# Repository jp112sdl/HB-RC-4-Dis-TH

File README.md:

# HB-RC-4-Dis-TH
## 4fach Wandtaster mit Display und Temperatursensor

Als Vorlage/Idee diente das [AVM FRITZ!DECT 440](https://avm.de/produkte/fritzdect/fritzdect-440/).

### Aufbau:

An den 4 Ecken befinden sich Taster, um über 4 verschiedenen Tasterkanäle Geräte zu steuern.<br/>
Unten mittig ist der Mode-Taster:
- langes Drücken = Anlernen oder (ganz lange) RESET
- kurzes Drücken = Anzeige der Tasterbeschriftung

In Ruhe werden auf dem Display die Temperatur (und wahlweise Luftfeuchtigkeit) sowie der Batteriezustand angezeigt.
Wird der Mode-Taster kurz gedrückt, erscheint für die in den Geräteeinstellungen festgelegte "Display Timeout" Zeit die Taster-Beschriftung.

Als Beschriftung lassen sich
- eine Überschrift (optional)
- 1 bis 2 Zeilen Beschriftungstext

hinterlegen

<br><br>

### Prototyp

Nur Temperaturanzeige:<br>
<br><br>
Temperatur- und Luftfeuchtigkeit:<br>
<br><br>
Tasterbeschriftungen:<br>

### PCB Version 2.1

<br>
**[Abstandhalter](https://github.com/jp112sdl/HB-RC-4-Dis-TH/blob/master/PCB/HB-RC-4-Dis-TH%20ePaper%20Spacer.stl) zwischen Platine und ePaper:**<br/>
<br/>

**erste Version von JLCPCB**

<br/>
<br/>

### CCU:

**Status und Bedienung -> Geräte**<br/>

<br/>
**Einstellungen -> Geräte**<br/>

### Zutaten
| Anzahl LiPo | Anzahl Batt | Bezeichnung | Bauform | Artikelnummer (Reichelt)|
|--------|--------|-------------|----------|---------------|
|6  |6  | 100nF	| 0805	| X7R-G0805 100N
|11	|11	| 1µF/25V	| 0805	| KEM X5R0805 1,0U
|1	|1	| 100µ/10V	| 3528	| TAJ 3528 100/10
|2	|0	| 10µ/10V	| 0805	|KEM X5R0805 10U
|1	|1 | LED rot	| 0805	| OSO LHR974
|1	|1	| LED grün	| 0805	| OSO LGR971
|1	|0	| LED weiß	| 0805	| SLO SMD-W0805-0
|3	|3	| MBR0530	| SOD-123	| MBR0530T1G ONS 
|1	|1	| 68µH	| 3012	| L-1616FPS 68µ
|1	|1	| IRLML 6346 | SOT-23	| IRLML 6346
|1	|1	| ATMEGA 1284P-AU	| TQFP-44	| ATMEGA 1284P-AU
|1  |0  | MCP 1700T-3002E | SOT-23 | MCP 1700T-3002E
|1  |0  | MCP 73831T-2ACI | SOT-23-5 | MCP 73831T-2ACI
|1  |0	| PC357 | SO-4 | PC 357NJ0000F |
|2	|2	| 240	| 0805	| RND 0805 1 240
|1	|0	| 680	| 0805	| RND 0805 1 680
|1	|0	| 1k 	| 0805	| RND 0805 1 1,0K
|1	|0	| 2k2	| 0805	| RND 0805 1 2,2K
|1	|0	| 4k7	| 0805	| RND 0805 1 4,7k
|3	|3	| 10k	| 0805	| RND 0805 1 10K
|3	|1	| 100k	| 0805	| RND 0805 1 100K
|1	|0	| 470k	| 0805	| RND 0805 1 470K
|2	|2	| 1,0	| 0805	| SMD-0805 1,00
|5	|5	| Taster	| THT	| RND 210-00193
|1	|1	| Taster	| SMD	| https://de.aliexpress.com/item/1005001298009129.html
|1	|1	| ZIF-Sockel 24pol.	| ZIF SMD	| EA WF050-24S
|1 |1	| GoodDisplay ePaper 1,54" GDEW0154M09 ||https://de.aliexpress.com/item/4000993819257.html|
|1 |1 | SHT31 Sensor ||https://de.aliexpress.com/item/32850554676.html|
|1	|0	| 600mAh LiPo	| 	| https://www.ebay.de/itm/LiPo-Lithium-Polymer-3-7V-Akku-mit-BMS-PCB-Batterie-Handy-MP3-Tablet-Navi-LiIon/372814314688?ssPageName=STRK%3AMEBIDX%3AIT&var=641708800610 
|1	|0	| Induktionsladeempfänger	1x1,5cm | 	| https://de.aliexpress.com/item/4000086798457.html
|1	|0	| Induktionsladegerät	| 	| https://de.aliexpress.com/item/4000969719130.html

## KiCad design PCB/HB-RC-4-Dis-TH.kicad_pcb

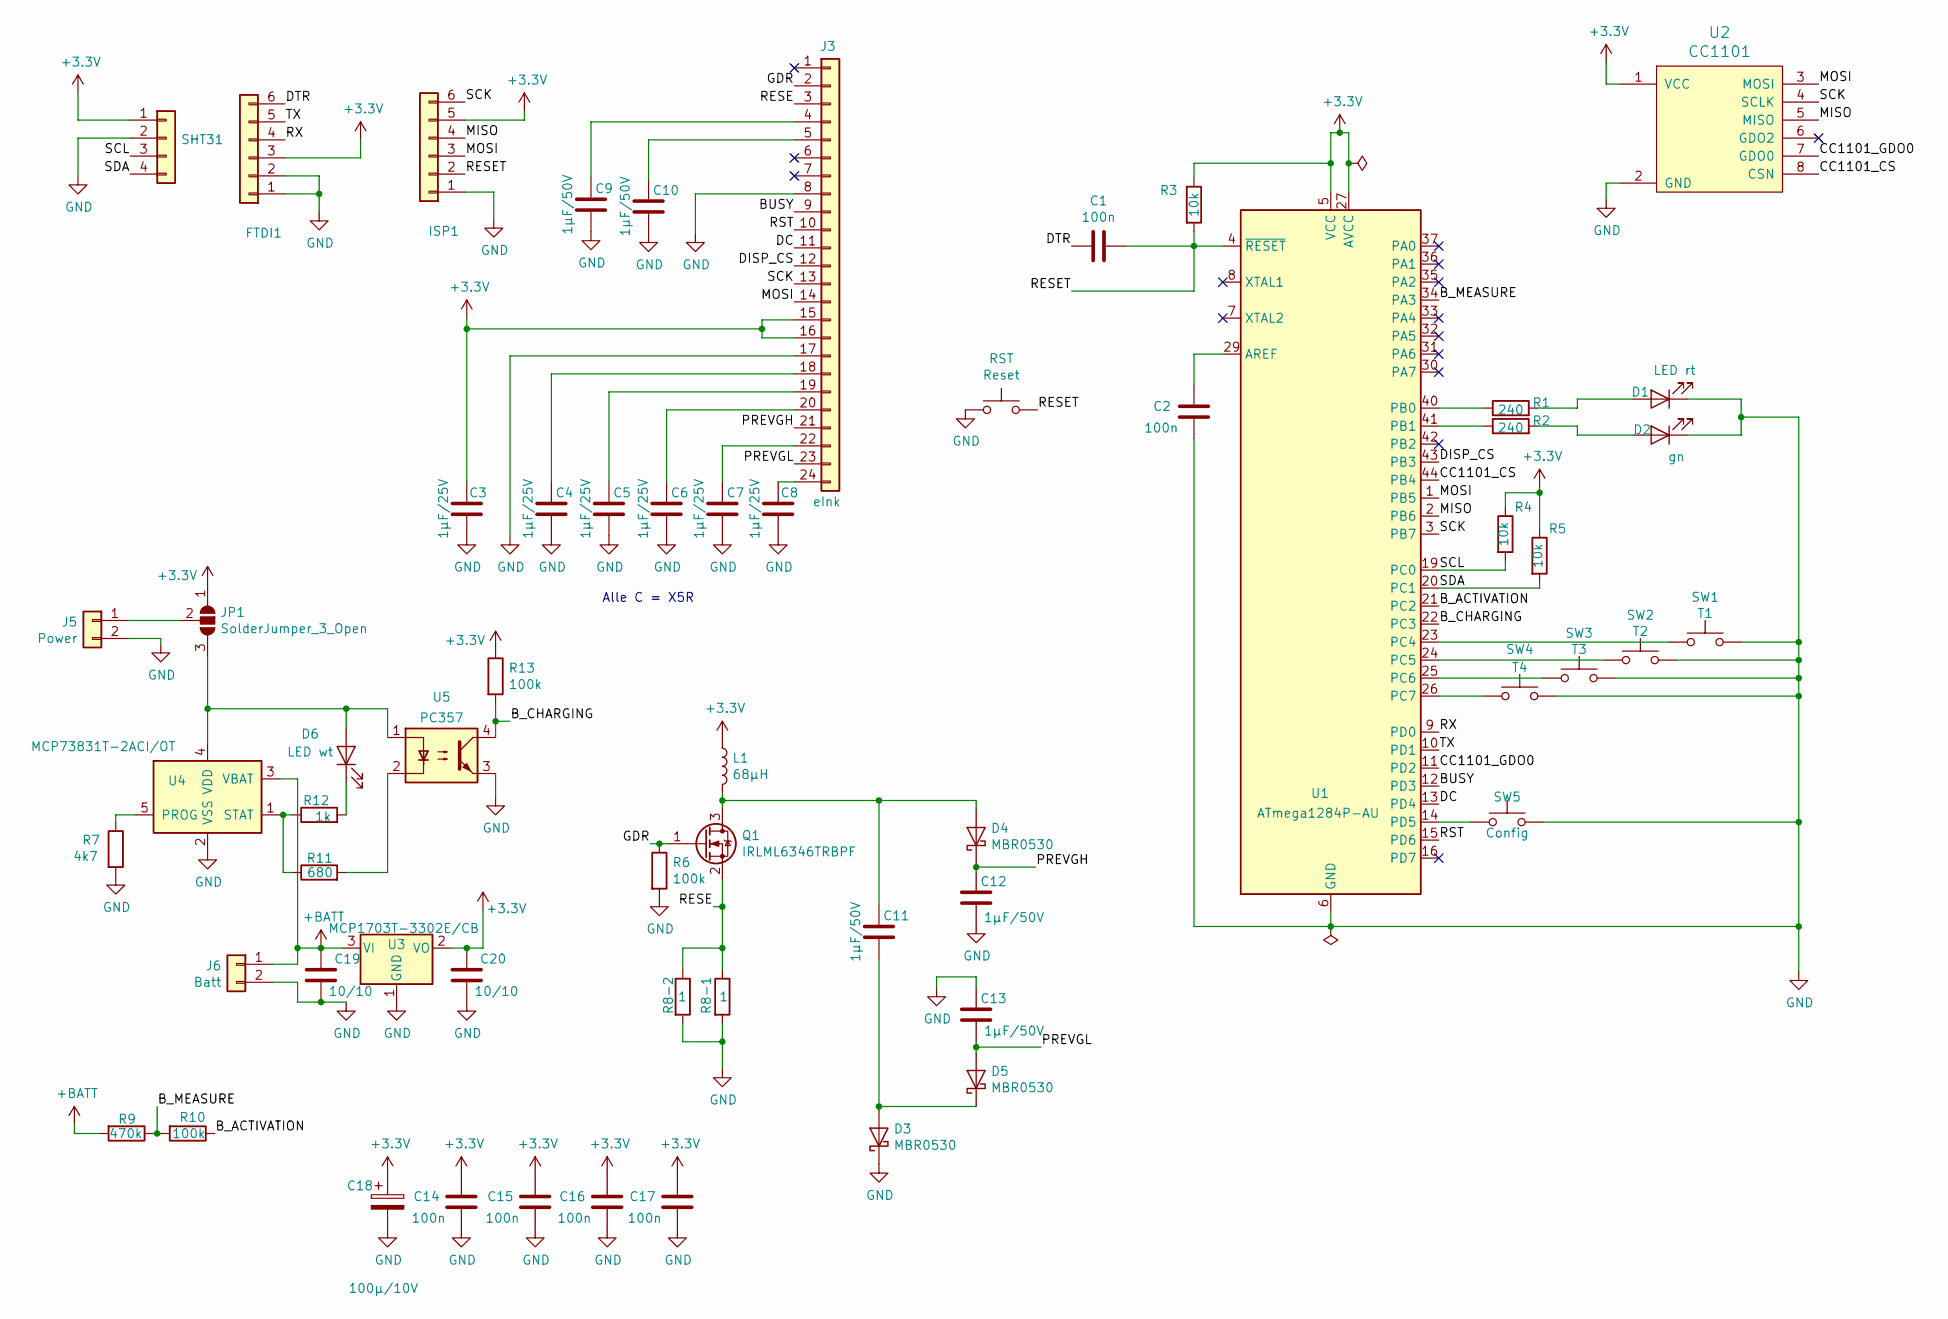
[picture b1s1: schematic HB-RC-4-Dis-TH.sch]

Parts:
C1, C2, C14, C15, C16, C17: 100n; C_0805_2012Metric_Pad1.15x1.40mm_HandSolder
C3, C4, C5, C6, C7, C8: 1µF/25V; C_0805_2012Metric_Pad1.15x1.40mm_HandSolder
C9, C10, C11, C12, C13: 1µF/50V; C_0805_2012Metric_Pad1.15x1.40mm_HandSolder
C18: 100µ/10V; CP_Tantalum_Case-B_EIA-3528-21_Hand
C19, C20: 10/10; C_0805_2012Metric_Pad1.15x1.40mm_HandSolder
D1: LED rt; LED_0805_2012Metric_Pad1.15x1.40mm_HandSolder
D2: gn; LED_0805_2012Metric_Pad1.15x1.40mm_HandSolder
D3, D4, D5: MBR0530; D_SOD-123
D6: LED wt; LED_0805_2012Metric_Pad1.15x1.40mm_HandSolder
FTDI1: FTDI; PinHeader_1x06_P2.54mm_Vertical
ISP1: ISP; PinPads_ISP
J3: eInk; Hirose_FH12-24S-0.5SH_1x24_P0.5mm_Horizontal
J5: Power; PinHeader_1x02_P2.54mm_Vertical
J6: Batt; PinHeader_1x02_P2.54mm_Vertical
JP1: SolderJumper_3_Open; SolderJumper-3_P1.3mm_Open_RoundedPad1.0x1.5mm
L1: 68µH; L_Wuerth_MAPI-3012
Q1: IRLML6346TRBPF; SOT-23
R1, R2: 240; R_0805_2012Metric_Pad1.15x1.40mm_HandSolder
R3, R4, R5: 10k; R_0805_2012Metric_Pad1.15x1.40mm_HandSolder
R6, R10, R13: 100k; R_0805_2012Metric_Pad1.15x1.40mm_HandSolder
R7: 4k7; R_0805_2012Metric_Pad1.15x1.40mm_HandSolder
R8-1, R8-2: 1; R_0805_2012Metric_Pad1.15x1.40mm_HandSolder
R9: 470k; R_0805_2012Metric_Pad1.15x1.40mm_HandSolder
R11: 680; R_0805_2012Metric_Pad1.15x1.40mm_HandSolder
R12: 1k; R_0805_2012Metric_Pad1.15x1.40mm_HandSolder
RST: Reset; SW_SPST_B3U-1000P
SHT31: SHT31; PinHeader_1x04_P2.54mm_Vertical
SW1: T1; SW_PUSH_6mm_H5mm
SW2: T2; SW_PUSH_6mm_H5mm
SW3: T3; SW_PUSH_6mm_H5mm
SW4: T4; SW_PUSH_6mm_H5mm
SW5: Config; SW_PUSH_6mm_H5mm
U1: ATmega1284P-AU; TQFP-44_10x10mm_P0.8mm
U2: CC1101; CC1101_Pads
U3: MCP1703T-3302E/CB; SOT-23
U4: MCP73831T-2ACI/OT; SOT-23-5
U5: PC357; SO-4_4.4x3.6mm_P2.54mm

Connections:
+3V3: C3.1, C14.1, C15.1, C16.1, C17.1, C18.1, C20.1, FTDI1.3, ISP1.5, J3.15, J3.16, JP1.1 (A), L1.1, R3.1, R4.1, R5.1, R13.1, SHT31.1, U1.5 (VCC), U1.17 (VCC), U1.27 (AVCC), U1.38 (VCC), U2.1 (VCC), U3.2 (VO)
+BATT: C19.1, J6.1, R9.2, U3.3 (VI), U4.3 (VBAT)
/BUSY: J3.9, U1.12 (PD3)
/B_ACTIVATION: R10.1, U1.21 (PC2)
/B_CHARGING: R13.2, U1.22 (PC3), U5.4
/B_MEASURE: R9.1, R10.2, U1.34 (PA3)
/CC1101_CS: U1.44 (PB4), U2.8 (CSN)
/CC1101_GDO0: U1.11 (PD2), U2.7 (GDO0)
/DC: J3.11, U1.13 (PD4)
/DISP_CS: J3.12, U1.43 (PB3)
/DTR: C1.2, FTDI1.6
/GDR: J3.2, Q1.1 (G), R6.1
/MISO: ISP1.4, U1.2 (PB6), U2.5 (MISO)
/MOSI: ISP1.3, J3.14, U1.1 (PB5), U2.3 (MOSI)
/PREVGH: C12.1, D4.1 (K), J3.21
/PREVGL: C13.2, D5.2 (A), J3.23
/RESE: J3.3, Q1.2 (S), R8-1.1, R8-2.1; also elsewhere on the board
/RESET: C1.1, ISP1.2, R3.2, RST.2, U1.4 (~RESET)
/RST: J3.10, U1.15 (PD6)
/RX: FTDI1.4, U1.9 (PD0)
/SCK: ISP1.6, J3.13, U1.3 (PB7), U2.4 (SCLK)
/SCL: R4.2, SHT31.3, U1.19 (PC0)
/SDA: R5.2, SHT31.4, U1.20 (PC1)
/TX: FTDI1.5, U1.10 (PD1)
GND: C2.2, C3.2, C4.2, C5.2, C6.2, C7.2, C8.2, C9.2, C10.2, C12.2, C13.1, C14.2, C15.2, C16.2, C17.2, C18.2, C19.2, C20.2, D1.1 (K), D2.1 (K), D3.1 (K), FTDI1.1, FTDI1.2, ISP1.1, J3.8, J3.17, J5.2, J6.2, R6.2, R7.2, R8-1.2, R8-2.2, RST.1, SHT31.2, SW1.2, SW2.2, SW3.2, SW4.2, SW5.2, U1.6 (GND), U1.18 (GND), U1.28 (GND), U1.39 (GND), U2.2 (GND), U3.1 (GND), U4.2 (VSS), U5.3; also elsewhere on the board
unnamed: C2.1, U1.29 (AREF)
unnamed: C4.1, J3.18
unnamed: C5.1, J3.19
unnamed: C6.1, J3.20
unnamed: C7.1, J3.22
unnamed: C8.1, J3.24
unnamed: C9.1, J3.4
unnamed: C10.1, J3.5
unnamed: C11.1, D4.2 (A), L1.2, Q1.3 (D)
unnamed: C11.2, D3.2 (A), D5.1 (K)
unnamed: D1.2 (A), R1.2
unnamed: D2.2 (A), R2.2
unnamed: D6.1 (K), R12.2
unnamed: D6.2 (A), JP1.3 (B), U4.4 (VDD), U5.1
unnamed: J5.1, JP1.2 (C)
unnamed: R1.1, U1.40 (PB0)
unnamed: R2.1, U1.41 (PB1)
unnamed: R7.1, U4.5 (PROG)
unnamed: R11.1, R12.1, U4.1 (STAT)
unnamed: R11.2, U5.2
unnamed: SW1.1, U1.23 (PC4)
unnamed: SW2.1, U1.24 (PC5)
unnamed: SW3.1, U1.25 (PC6)
unnamed: SW4.1, U1.26 (PC7)
unnamed: SW5.1, U1.14 (PD5)

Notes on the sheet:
Alle C = X5R

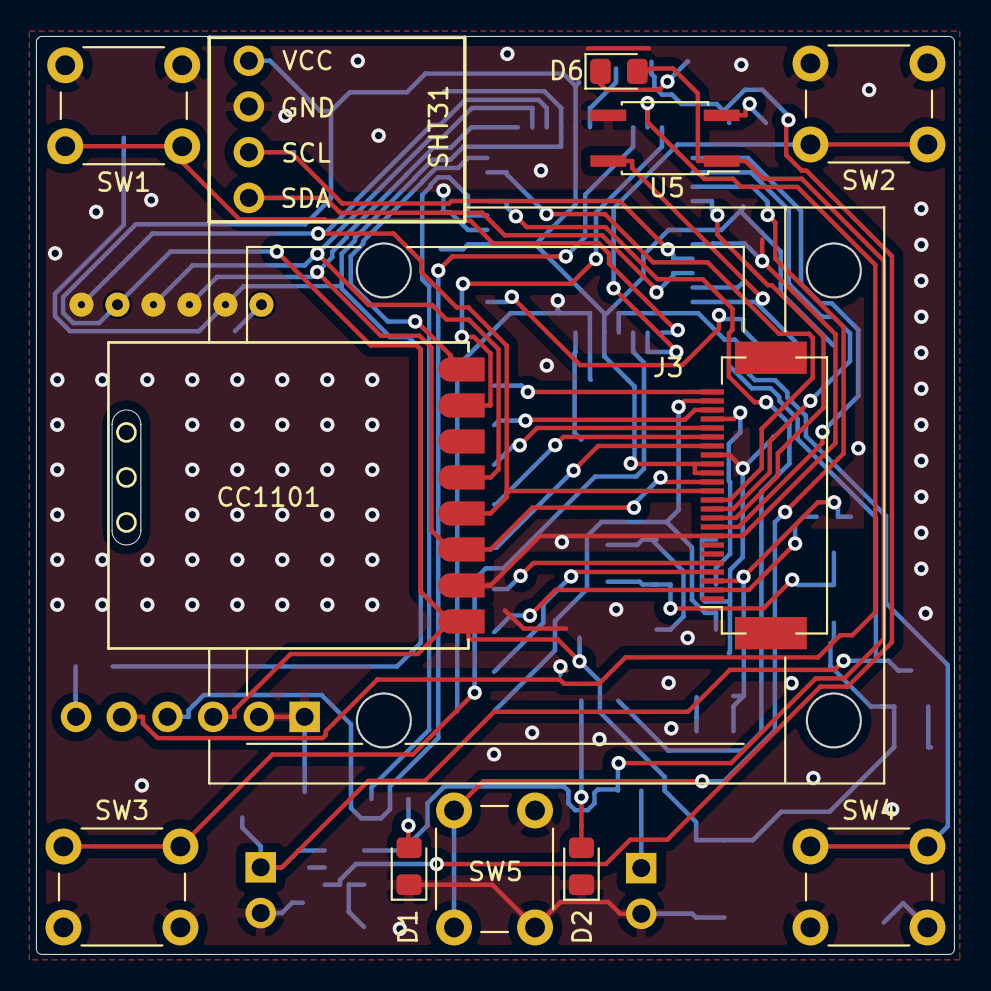
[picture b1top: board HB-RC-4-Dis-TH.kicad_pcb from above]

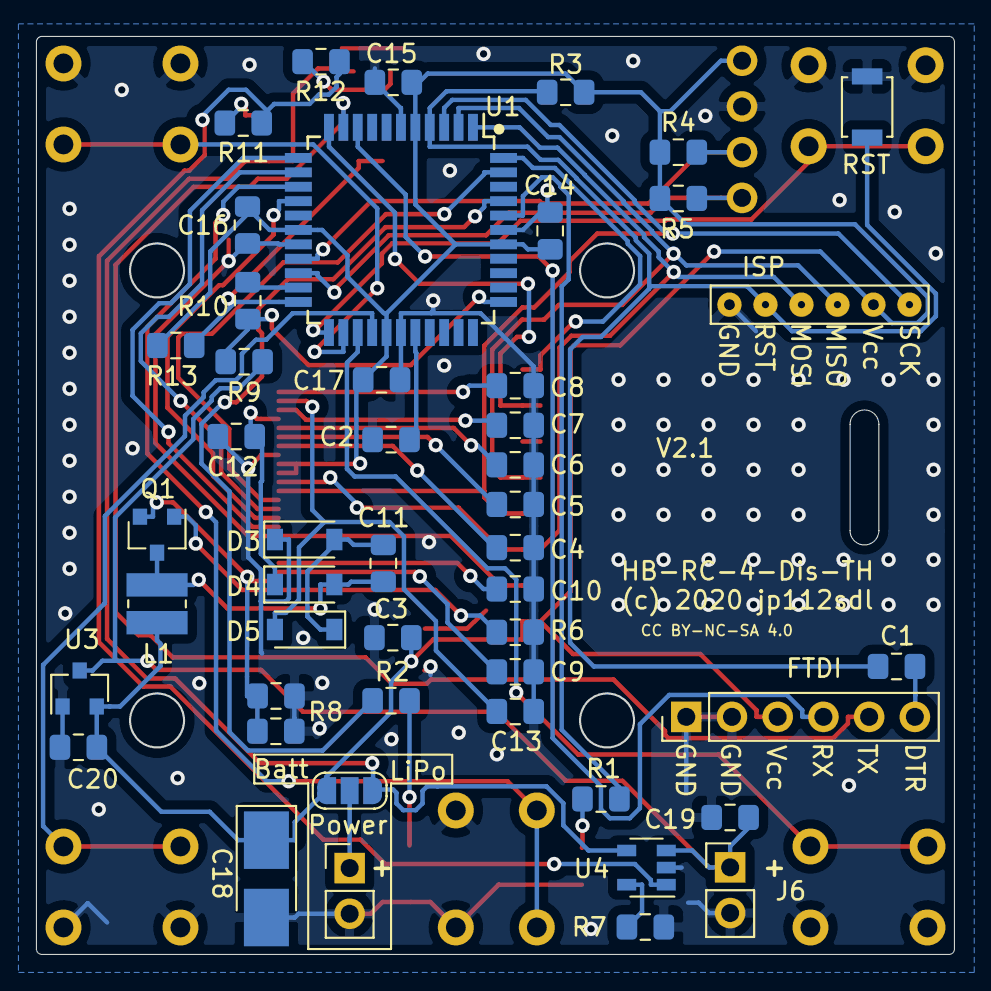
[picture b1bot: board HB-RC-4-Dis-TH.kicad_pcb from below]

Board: 2 copper layers, 50.9 x 50.9 mm, 60 parts (48 on the bottom side), 50 nets.

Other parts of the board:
R8: 1; R_0805_2012Metric_Pad1.15x1.40mm_HandSolder

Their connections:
/RESE: R8.1; also elsewhere on the board
GND: R8.2; also elsewhere on the board

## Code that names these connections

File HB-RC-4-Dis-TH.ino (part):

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    attachInterrupt(digitalPinToInterrupt(pin),__##pin##ISRHandler::isr,CHANGE);

#define V_BATT_MAX          40
#define B_CHARGING_PIN      25
#define BATTERY_MEASUREMENT IrqExternalBatt<A4, 24>
#define DEVICE_MODEL        {0xf3, 0x2e}
#define ADDITIONAL_CHANNELS 2
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  #define ASKSIN_PLUS_PLUS_VERSION_STR ASKSIN_PLUS_PLUS_VERSION
#endif

#define CC1101_CS_PIN       10 // PB4
#define CC1101_GDO0_PIN      2 // PD2
#define BTN01_PIN           26 // PC4
#define BTN02_PIN           27 // PC5
#define BTN03_PIN           28 // PC6
#define BTN04_PIN           29 // PC7
#define CONFIG_BUTTON_PIN    8 // PD5
#define LED_PIN_1            5 // PB1
#define LED_PIN_2            4 // PB0

#define TEXT_LENGTH               10
#define PEERS_PER_CHANNEL          8
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  {0x00, 0x00}              // Info Bytes
};

typedef LibSPI<CC1101_CS_PIN> SPIType;
typedef Radio<SPIType, CC1101_GDO0_PIN> RadioType;
typedef DualStatusLed<LED_PIN_1, LED_PIN_2> LedType;
typedef AskSin<LedType, BATTERY_MEASUREMENT, RadioType> Hal;
Hal hal;
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  remoteChannelISR(sdev.btnChannel(3), BTN03_PIN);
  remoteChannelISR(sdev.btnChannel(4), BTN04_PIN);
#ifdef USE_LIPO
  sdev.crgChannel().init(B_CHARGING_PIN);
  sdev.crgChannel().changed(true);
#endif

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
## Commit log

2020-08-05 major improvements
2020-08-09 put display class in separate header files
2020-08-09 remove comment
2020-08-10 code update
2020-08-10 add images
2020-08-15 changed position of temperature value
2020-08-15 add PCB
2020-08-15 fixed size
2020-08-15 update pcb
2020-08-15 add epaper display spacer stl
2020-08-15 add image
2020-08-15 add via
2020-08-16 update pcb v1.1 (added decoupling capacitors)
2020-08-19 enable deep sleep
2020-08-19 use multiple pin layouts
2020-08-25 modified pins for pcb
2020-08-25 changed resistor values
2020-08-25 update spacer
2020-08-25 update images
2020-08-26 shrink pcb to 51x51
2020-09-01 change AVR to 1284P
2020-09-06 add BOM
2020-09-06 add battery empty symbol and function to display temperature in .5 degree steps
2020-09-06 fix battery symbol
2020-10-11 replaced 3.3V LDO with 3.0V
2020-10-11 upbade bom
2020-11-13 add some docs
2020-12-03 added temperature/humidity offset
2021-01-19 add ibom
2023-04-09 bugfix

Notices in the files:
HB-RC-4-Dis-TH.ino:
2016-10-31 papa Creative Commons - http://creativecommons.org/licenses/by-nc-sa/3.0/de
2020-08-01 jp112sdl Creative Commons - http://creativecommons.org/licenses/by-nc-sa/3.0/de
PCB/HB-RC-4-Dis-TH.kicad_pcb:
CC BY-NC-SA 4.0
(c) 2020 jp112sdl
